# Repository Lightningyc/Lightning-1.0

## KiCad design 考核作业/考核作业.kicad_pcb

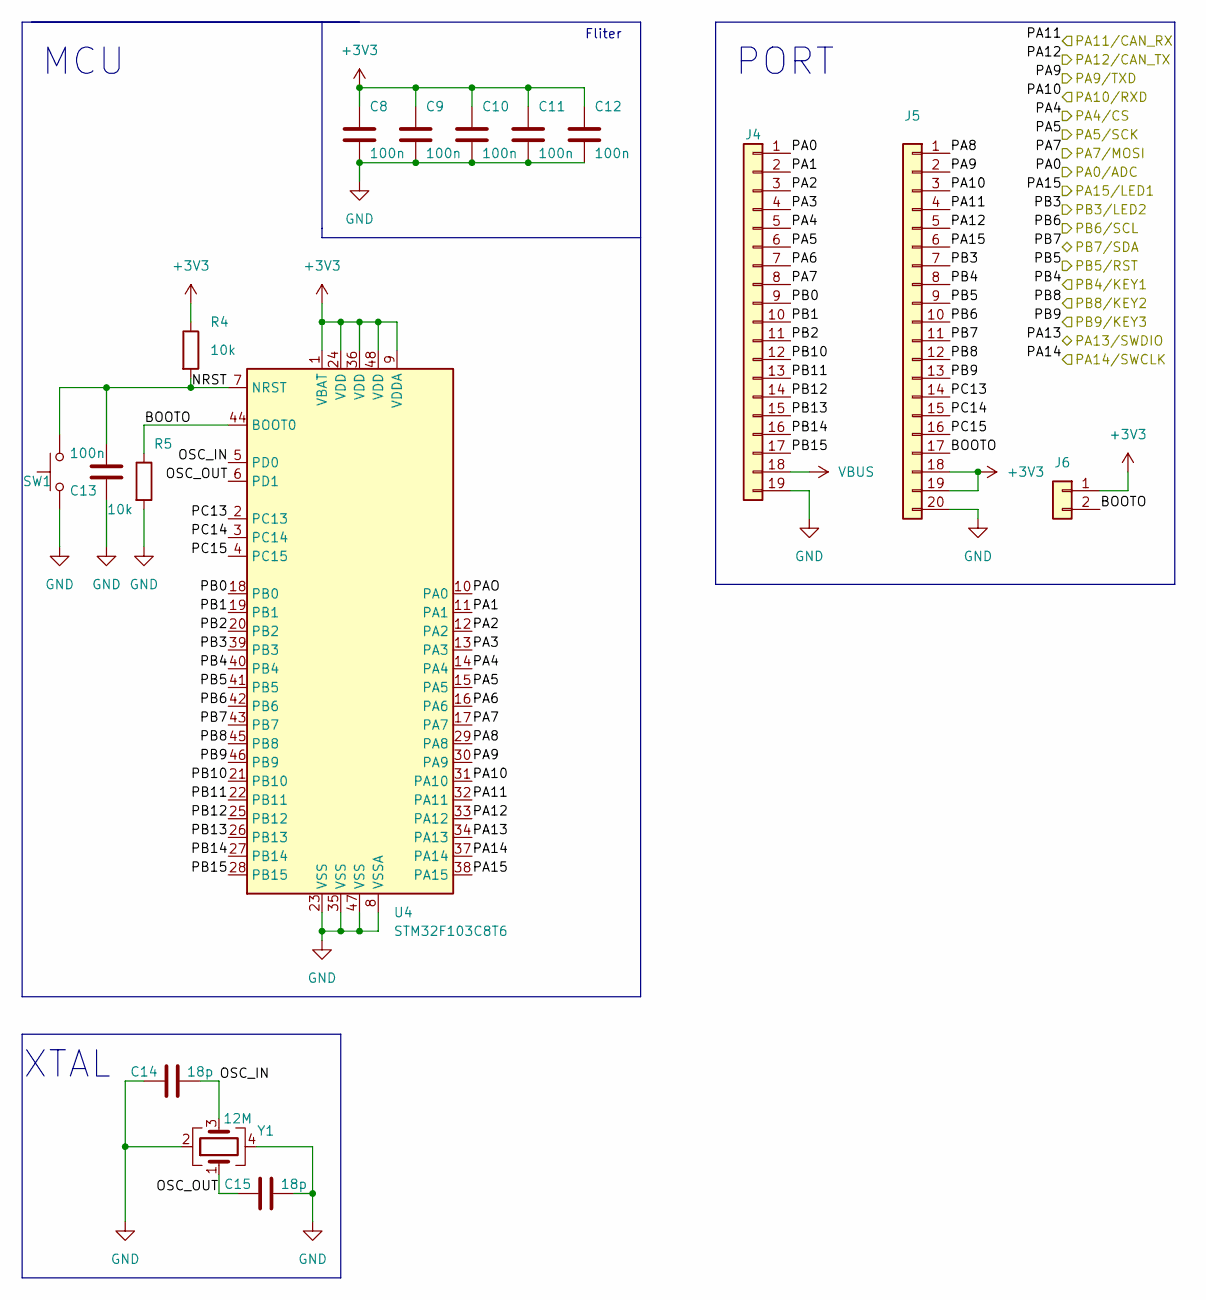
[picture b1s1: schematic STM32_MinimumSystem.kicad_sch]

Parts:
C8, C9, C10, C11, C12, C13: 100n; C_0603_1608Metric
C14, C15: 18p; C_0603_1608Metric
J4: Conn_01x19; PinHeader_1x19_P2.54mm_Vertical
J5: Conn_01x20; PinHeader_1x20_P2.54mm_Vertical
J6: Conn_01x02; PinHeader_1x02_P2.54mm_Vertical
R4, R5: 10k; R_0603_1608Metric
SW1: SW_Push; SW_Push_1P1T_NO_6x6mm_H9.5mm
U4: STM32F103C8T6; LQFP-48_7x7mm_P0.5mm
Y1: 12M; Crystal_SMD_3225-4Pin_3.2x2.5mm

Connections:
+3V3: C8.1, C9.1, C10.1, C11.1, C12.1, J5.18, J5.19, J6.1, R4.1, U4.1 (VBAT), U4.9 (VDDA), U4.24 (VDD), U4.36 (VDD), U4.48 (VDD); also elsewhere on the board
/STM32_MinimumSystem/BOOTO: J5.17, J6.2, R5.1, U4.44 (BOOT0)
/STM32_MinimumSystem/NRST: C13.1, R4.2, SW1.2, U4.7 (NRST)
/STM32_MinimumSystem/OSC_IN: C14.1, U4.5 (PD0), Y1.3
/STM32_MinimumSystem/OSC_OUT: C15.2, U4.6 (PD1), Y1.1
/STM32_MinimumSystem/PA0: J4.1; also elsewhere on the board
/STM32_MinimumSystem/PA1: J4.2, U4.11 (PA1)
/STM32_MinimumSystem/PA2: J4.3, U4.12 (PA2)
/STM32_MinimumSystem/PA3: J4.4, U4.13 (PA3)
/STM32_MinimumSystem/PA4: J4.5, U4.14 (PA4); also elsewhere on the board
/STM32_MinimumSystem/PA5: J4.6, U4.15 (PA5); also elsewhere on the board
/STM32_MinimumSystem/PA6: J4.7, U4.16 (PA6)
/STM32_MinimumSystem/PA7: J4.8, U4.17 (PA7); also elsewhere on the board
/STM32_MinimumSystem/PA8: J5.1, U4.29 (PA8)
/STM32_MinimumSystem/PA9: J5.2, U4.30 (PA9); also elsewhere on the board
/STM32_MinimumSystem/PA10: J5.3, U4.31 (PA10); also elsewhere on the board
/STM32_MinimumSystem/PA11: J5.4, U4.32 (PA11); also elsewhere on the board
/STM32_MinimumSystem/PA12: J5.5, U4.33 (PA12); also elsewhere on the board
/STM32_MinimumSystem/PA13: U4.34 (PA13); also elsewhere on the board
/STM32_MinimumSystem/PA14: U4.37 (PA14); also elsewhere on the board
/STM32_MinimumSystem/PA15: J5.6, U4.38 (PA15); also elsewhere on the board
/STM32_MinimumSystem/PAO: U4.10 (PA0)
/STM32_MinimumSystem/PB0: J4.9, U4.18 (PB0)
/STM32_MinimumSystem/PB1: J4.10, U4.19 (PB1)
/STM32_MinimumSystem/PB2: J4.11, U4.20 (PB2)
/STM32_MinimumSystem/PB3: J5.7, U4.39 (PB3); also elsewhere on the board
/STM32_MinimumSystem/PB4: J5.8, U4.40 (PB4); also elsewhere on the board
/STM32_MinimumSystem/PB5: J5.9, U4.41 (PB5)
/STM32_MinimumSystem/PB6: J5.10, U4.42 (PB6)
/STM32_MinimumSystem/PB7: J5.11, U4.43 (PB7)
/STM32_MinimumSystem/PB8: J5.12, U4.45 (PB8); also elsewhere on the board
/STM32_MinimumSystem/PB9: J5.13, U4.46 (PB9); also elsewhere on the board
/STM32_MinimumSystem/PB10: J4.12, U4.21 (PB10)
/STM32_MinimumSystem/PB11: J4.13, U4.22 (PB11)
/STM32_MinimumSystem/PB12: J4.14, U4.25 (PB12)
/STM32_MinimumSystem/PB13: J4.15, U4.26 (PB13)
/STM32_MinimumSystem/PB14: J4.16, U4.27 (PB14)
/STM32_MinimumSystem/PB15: J4.17, U4.28 (PB15)
/STM32_MinimumSystem/PC13: J5.14, U4.2 (PC13)
/STM32_MinimumSystem/PC14: J5.15, U4.3 (PC14)
/STM32_MinimumSystem/PC15: J5.16, U4.4 (PC15)
GND: C8.2, C9.2, C10.2, C11.2, C12.2, C13.2, C14.2, C15.1, J4.19, J5.20, R5.2, SW1.1, U4.8 (VSSA), U4.23 (VSS), U4.35 (VSS), U4.47 (VSS), Y1.2, Y1.4; also elsewhere on the board
VBUS: J4.18; also elsewhere on the board

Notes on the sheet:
Fliter
XTAL
MCU
PORT

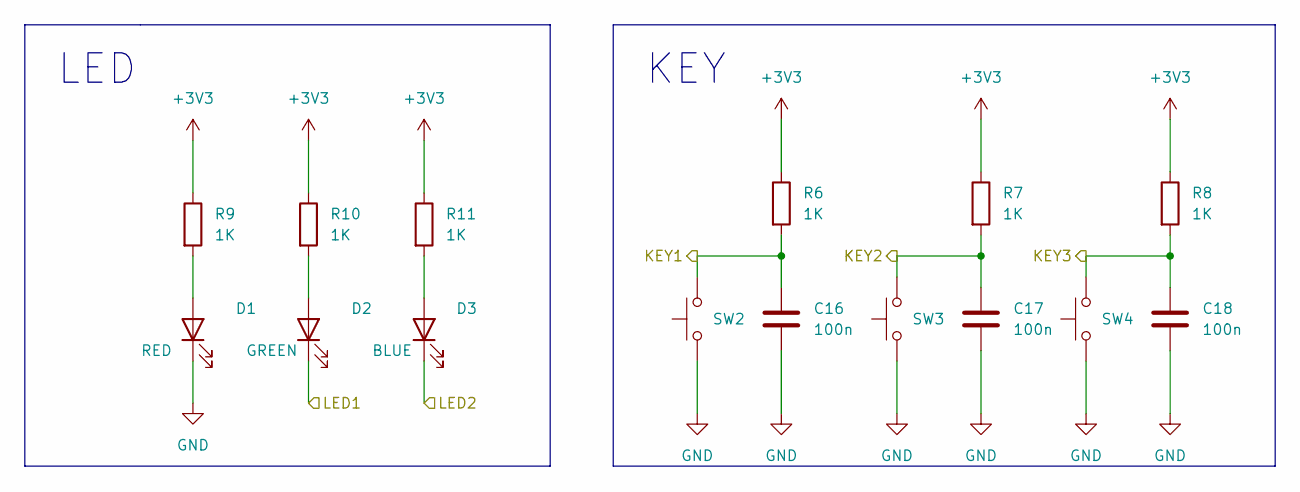
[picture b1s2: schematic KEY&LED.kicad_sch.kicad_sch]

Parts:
C16, C17, C18: 100n; C_0603_1608Metric
D1: RED; LED_0603_1608Metric
D2: GREEN; LED_0603_1608Metric
D3: BLUE; LED_0603_1608Metric
R6, R7, R8, R9, R10, R11: 1K; R_0603_1608Metric
SW2, SW3, SW4: SW_Push; SW_Push_1P1T_NO_6x6mm_H9.5mm

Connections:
+3V3: R6.1, R7.1, R8.1, R9.1, R10.1, R11.1; also elsewhere on the board
/STM32_MinimumSystem/PA15: D2.1 (K); also elsewhere on the board
/STM32_MinimumSystem/PB3: D3.1 (K); also elsewhere on the board
/STM32_MinimumSystem/PB4: C16.1, R6.2, SW2.2; also elsewhere on the board
/STM32_MinimumSystem/PB8: C17.1, R7.2, SW3.2; also elsewhere on the board
/STM32_MinimumSystem/PB9: C18.1, R8.2, SW4.2; also elsewhere on the board
GND: C16.2, C17.2, C18.2, D1.1 (K), SW2.1, SW3.1, SW4.1; also elsewhere on the board
unnamed: D1.2 (A), R9.2
unnamed: D2.2 (A), R10.2
unnamed: D3.2 (A), R11.2

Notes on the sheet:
KEY
LED

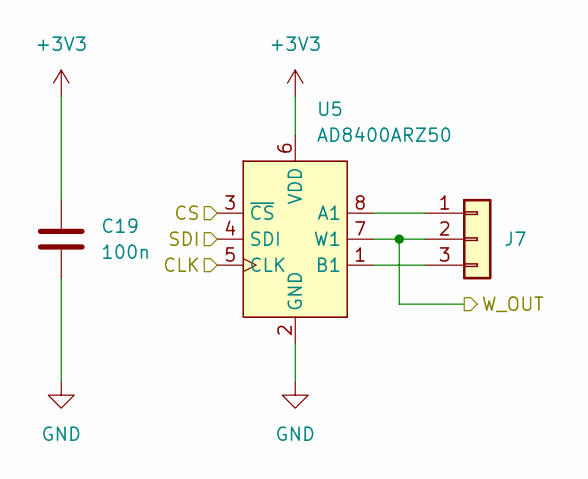
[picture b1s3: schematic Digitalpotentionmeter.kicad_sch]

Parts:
C19: 100n; C_0603_1608Metric
J7: Conn_01x03; PinHeader_1x03_P2.54mm_Vertical
U5: AD8400ARZ50; SOP-8_3.9x4.9mm_P1.27mm

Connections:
+3V3: C19.1, U5.6 (VDD); also elsewhere on the board
/STM32_MinimumSystem/PA0: J7.2, U5.7 (W1); also elsewhere on the board
/STM32_MinimumSystem/PA4: U5.3 (~CS); also elsewhere on the board
/STM32_MinimumSystem/PA5: U5.5 (CLK); also elsewhere on the board
/STM32_MinimumSystem/PA7: U5.4 (SDI); also elsewhere on the board
GND: C19.2, U5.2 (GND); also elsewhere on the board
unnamed: J7.1, U5.8 (A1)
unnamed: J7.3, U5.1 (B1)

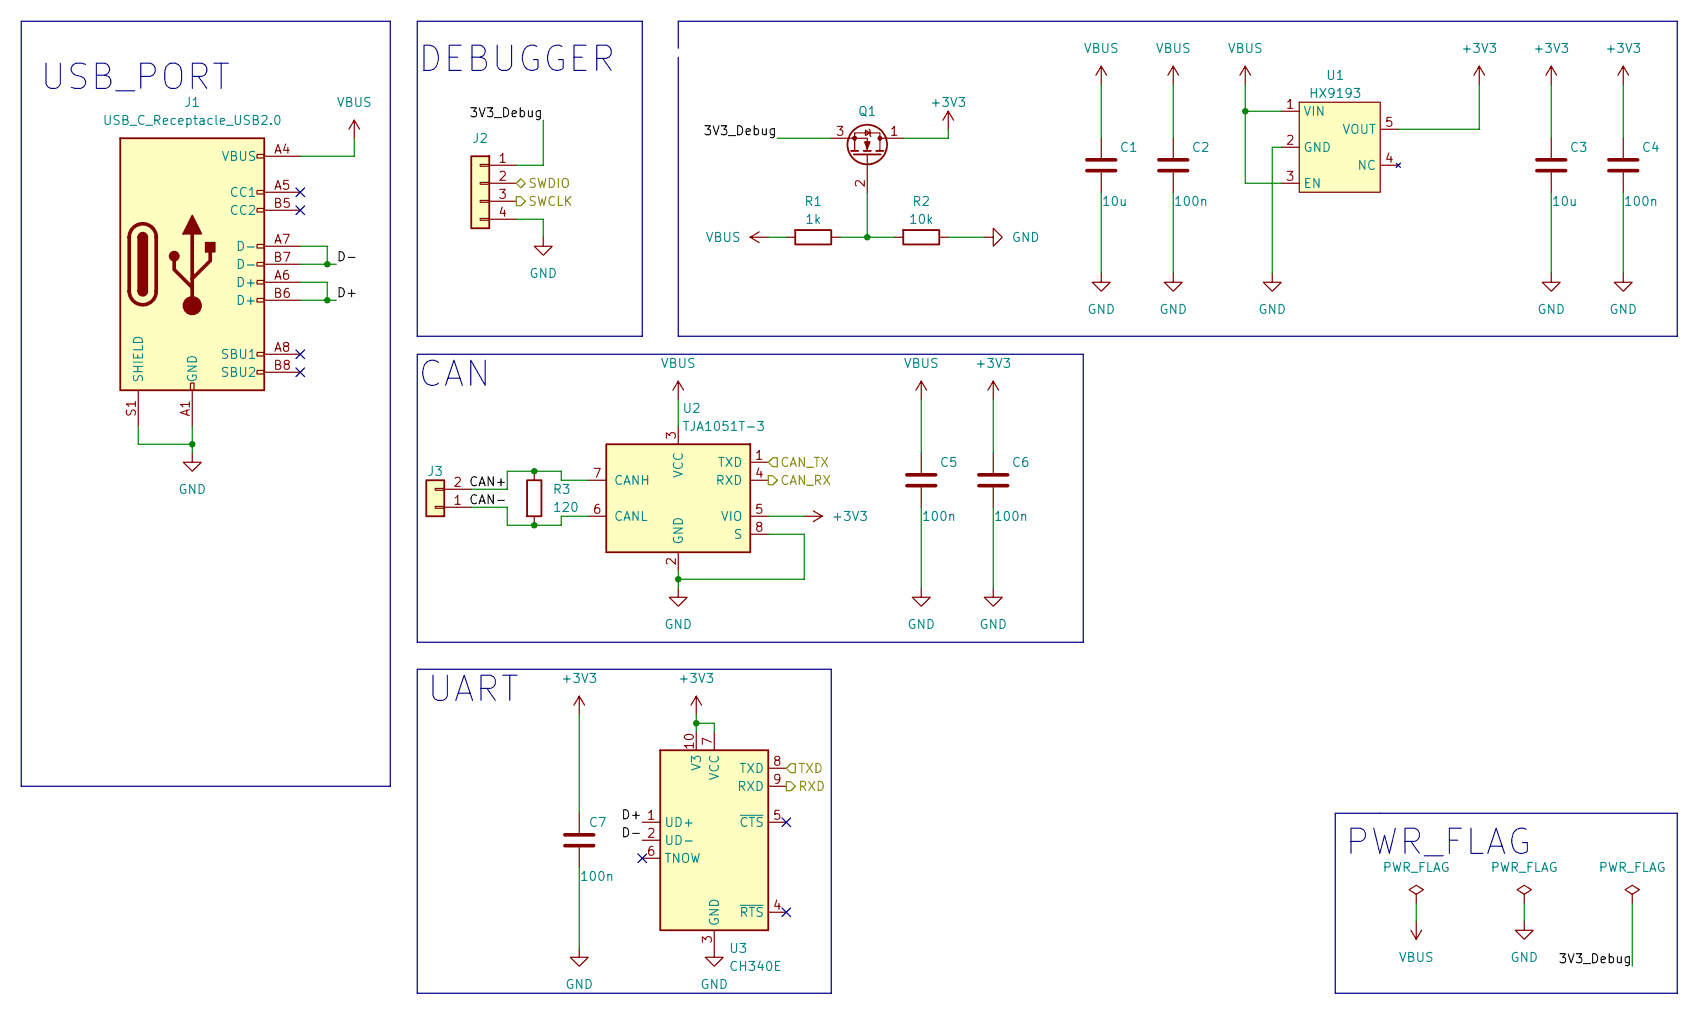
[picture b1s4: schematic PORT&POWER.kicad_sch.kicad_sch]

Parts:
C1, C3: 10u; C_0603_1608Metric
C2, C4, C5, C6, C7: 100n; C_0603_1608Metric
J1: USB_C_Receptacle_USB2.0; USB_C_Receptacle_Palconn_UTC16-G
J2: Conn_01x04; PinHeader_1x04_P2.54mm_Vertical
J3: Conn_01x02; JST_GH_SM02B-GHS-TB_1x02-1MP_P1.25mm_Horizontal
Q1: Q_NMOS_DGS; TSOT-23
R1: 1k; R_0603_1608Metric
R2: 10k; R_0603_1608Metric
R3: 120; R_0603_1608Metric
U1: HX9193; SOT-23-5_HandSoldering
U2: TJA1051T-3; SOIC-8_3.9x4.9mm_P1.27mm
U3: CH340E; MSOP-10_3x3mm_P0.5mm

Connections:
+3V3: C3.1, C4.1, C6.1, C7.1, Q1.1 (D), U1.5 (VOUT), U2.5 (VIO), U3.7 (VCC), U3.10 (V3); also elsewhere on the board
/PORT&POWER/3V3_Debug: J2.1, Q1.3 (S)
/PORT&POWER/CAN+: J3.2, R3.1, U2.7 (CANH)
/PORT&POWER/CAN-: J3.1, R3.2, U2.6 (CANL)
/PORT&POWER/D+: J1.A6 (D+), J1.B6 (D+), U3.1 (UD+)
/PORT&POWER/D-: J1.A7 (D-), J1.B7 (D-), U3.2 (UD-)
/STM32_MinimumSystem/PA9: U3.8 (TXD); also elsewhere on the board
/STM32_MinimumSystem/PA10: U3.9 (RXD); also elsewhere on the board
/STM32_MinimumSystem/PA11: U2.4 (RXD); also elsewhere on the board
/STM32_MinimumSystem/PA12: U2.1 (TXD); also elsewhere on the board
/STM32_MinimumSystem/PA13: J2.2; also elsewhere on the board
/STM32_MinimumSystem/PA14: J2.3; also elsewhere on the board
GND: C1.2, C2.2, C3.2, C4.2, C5.2, C6.2, C7.2, J1.A1 (GND), J1.A12 (GND), J1.B1 (GND), J1.B12 (GND), J1.S1 (SHIELD), J2.4, R2.1, U1.2 (GND), U2.2 (GND), U2.8 (S), U3.3 (GND); also elsewhere on the board
unnamed: Q1.2 (G), R1.1, R2.2
VBUS: C1.1, C2.1, C5.1, J1.A4 (VBUS), J1.A9 (VBUS), J1.B4 (VBUS), J1.B9 (VBUS), R1.2, U1.1 (VIN), U1.3 (EN), U2.3 (VCC); also elsewhere on the board

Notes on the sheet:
CAN
DEBUGGER
PWR_FLAG
UART
USB_PORT

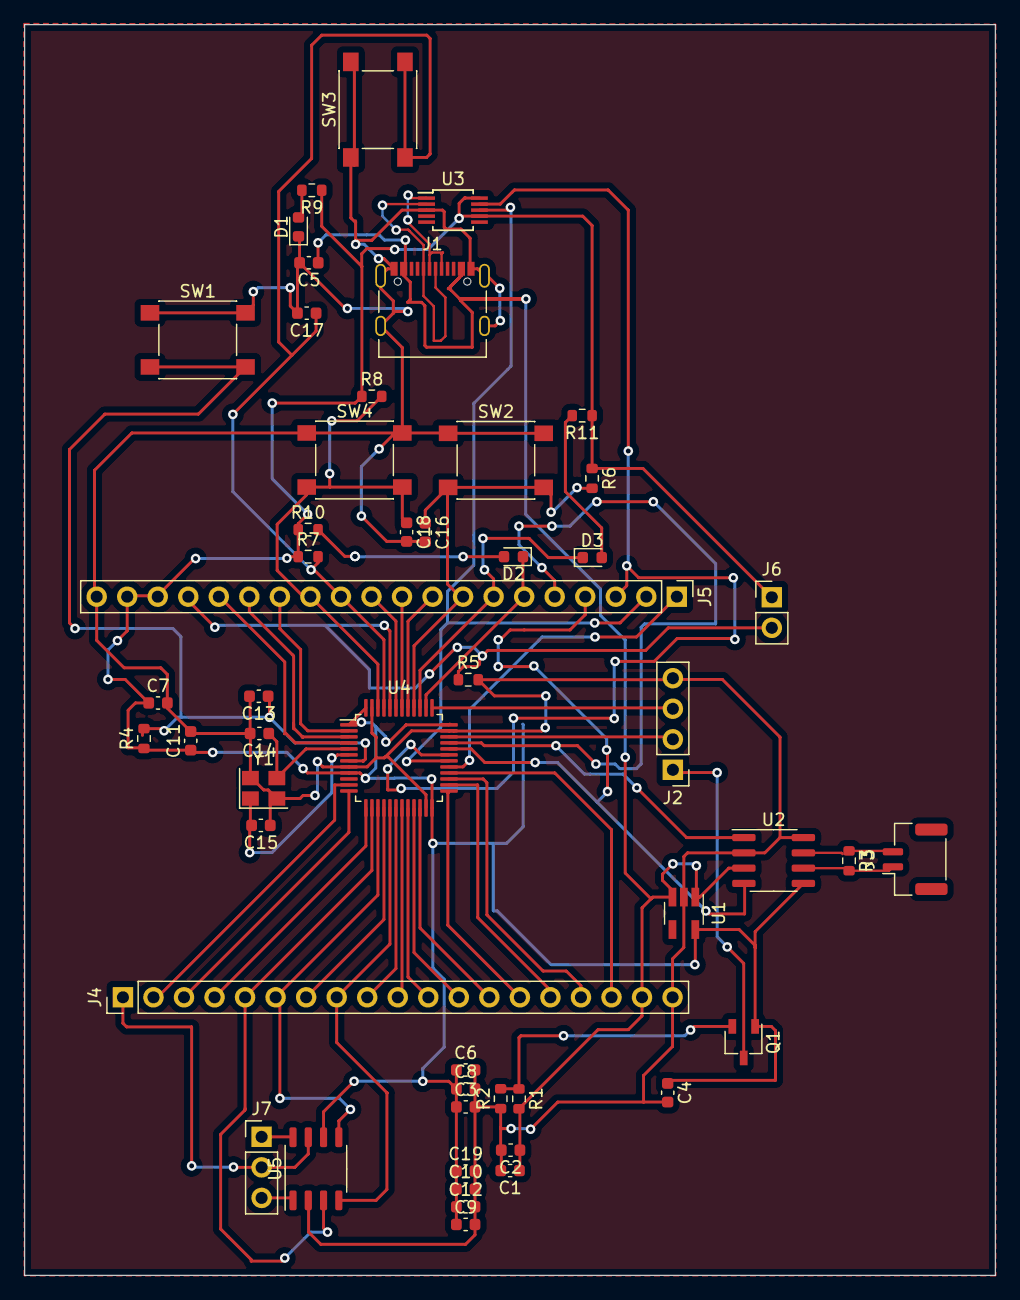
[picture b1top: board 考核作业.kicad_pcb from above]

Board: 2 copper layers, 80.7 x 104.0 mm, 51 parts (0 on the bottom side), 53 nets.

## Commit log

2022-10-20 add sth
2022-10-22 1223
2022-10-22 添加敷铜
2022-10-22 添加文件
2022-10-26 polish sth
2022-10-26 README
2022-10-27 随便写写
2022-10-28 add document
2022-10-28 改点东西
2022-10-28 没事删删
2022-10-29 1213
2022-10-29 12221
